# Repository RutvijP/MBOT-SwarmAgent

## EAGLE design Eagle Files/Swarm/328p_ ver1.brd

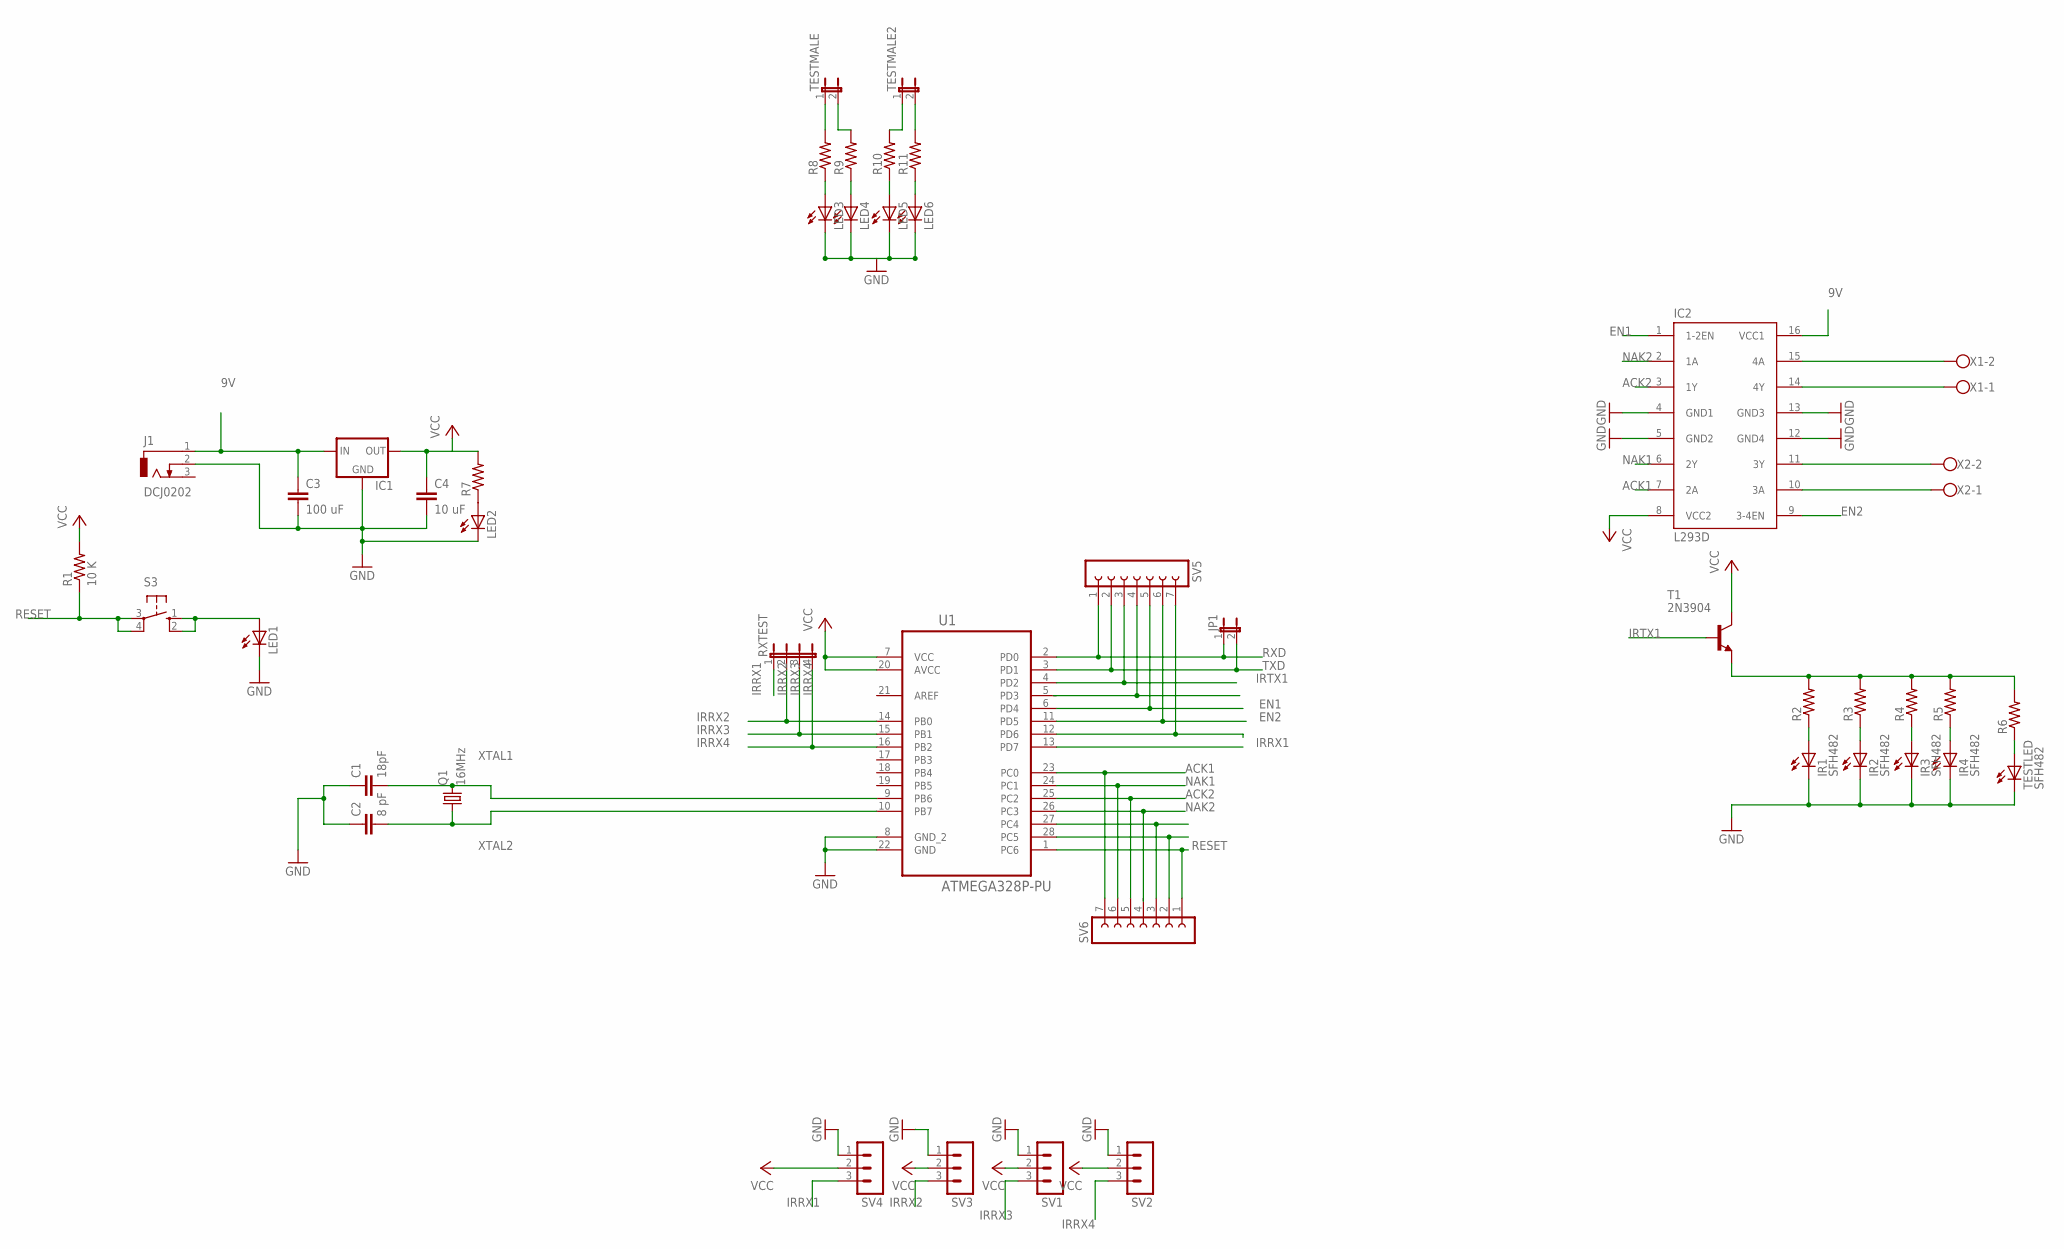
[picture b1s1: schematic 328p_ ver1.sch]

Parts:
C1: 18pF; C2.5-3
C2: 8 pF; C2.5-3
C3: 100 uF; C2.5-3
C4: 10 uF; C2.5-3
IC1: 78XXS
IC2: L293D; DIL16
IR1, IR2, IR3, IR4: SFH482
J1: DCJ0202
JP1: JP1E; JP1
LED1, LED2, LED3, LED4, LED5, LED6: LED3MM
Q1: 16MHz; HC49/S
R1: 10 K; 0207/12
R2, R3, R4, R5, R6, R7, R8, R9, R10, R11: R-US_0204/7; 0204/7
RXTEST: JP4E; JP4
S3: 10-XX; B3F-10XX
SV1, SV2, SV3, SV4: MA03-1
SV5, SV6: FE07-1; FE07
T1: 2N3904; TO92
TESTLED: SFH482
TESTMALE, TESTMALE2: JP1E; JP1
U1: ATMEGA328P-PU; DIP254P762X457-28
X1, X2: W237-102

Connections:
9V: C3.1, IC1.IN, IC2.16 (VCC1), J1.1
ACK1: IC2.7 (2A), SV6.7, U1.23 (PC0)
ACK2: IC2.3 (1Y), SV6.5, U1.25 (PC2)
EN1: IC2.1 (1-2EN), SV5.5, U1.6 (PD4)
EN2: IC2.9 (3-4EN), SV5.6, U1.11 (PD5)
GND: C1.1, C2.1, C3.2, C4.2, IC1.GND, IC2.4 (GND1), IC2.5 (GND2), IC2.12 (GND4), IC2.13 (GND3), IR1.K (C), IR2.K (C), IR3.K (C), IR4.K (C), J1.2, LED1.K (C), LED2.K (C), LED3.K (C), LED4.K (C), LED5.K (C), LED6.K (C), SV1.1, SV2.1, SV3.1, SV4.1, TESTLED.K (C), U1.8 (GND_2), U1.22 (GND)
IRRX1: RXTEST.1, SV4.3, U1.13 (PD7)
IRRX2: RXTEST.2, SV3.3, U1.14 (PB0)
IRRX3: RXTEST.3, SV1.3, U1.15 (PB1)
IRRX4: RXTEST.4, SV2.3, U1.16 (PB2)
IRTX1: SV5.3, T1.2 (B), U1.4 (PD2)
unnamed: IC2.15 (4A), X1.2
unnamed: IR1.A, R2.1
unnamed: IR2.A, R3.1
unnamed: IR3.A, R4.1
unnamed: IR4.A, R5.1
unnamed: R2.2, R3.2, R4.2, R5.2, R6.2, T1.3 (E)
unnamed: IC2.14 (4Y), X1.1
unnamed: IC2.11 (3Y), X2.2
unnamed: IC2.10 (3A), X2.1
unnamed: R6.1, TESTLED.A
unnamed: LED2.A, R7.1
unnamed: R8.2, TESTMALE.1
unnamed: LED3.A, R8.1
unnamed: LED1.A, S3.1 (S), S3.2 (S1)
unnamed: R9.2, TESTMALE.2
unnamed: LED4.A, R9.1
unnamed: R10.2, TESTMALE2.1
unnamed: R11.2, TESTMALE2.2
unnamed: LED6.A, R11.1
unnamed: LED5.A, R10.1
unnamed: SV5.7, U1.12 (PD6)
unnamed: SV6.3, U1.27 (PC4)
unnamed: SV6.2, U1.28 (PC5)
NAK1: IC2.6 (2Y), SV6.6, U1.24 (PC1)
NAK2: IC2.2 (1A), U1.26 (PC3)
RESET: R1.1, S3.3, S3.4 (P1), SV6.1, U1.1 (PC6)
RXD: JP1.1, SV5.1, U1.2 (PD0)
TXD: JP1.2, SV5.2, U1.3 (PD1)
VCC: C4.1, IC1.OUT, IC2.8 (VCC2), R1.2, R7.2, SV1.2, SV2.2, SV3.2, SV4.2, T1.1 (C), U1.7 (VCC), U1.20 (AVCC)
XTAL1: C1.2, Q1.2, U1.9 (PB6)
XTAL2: C2.2, Q1.1, U1.10 (PB7)

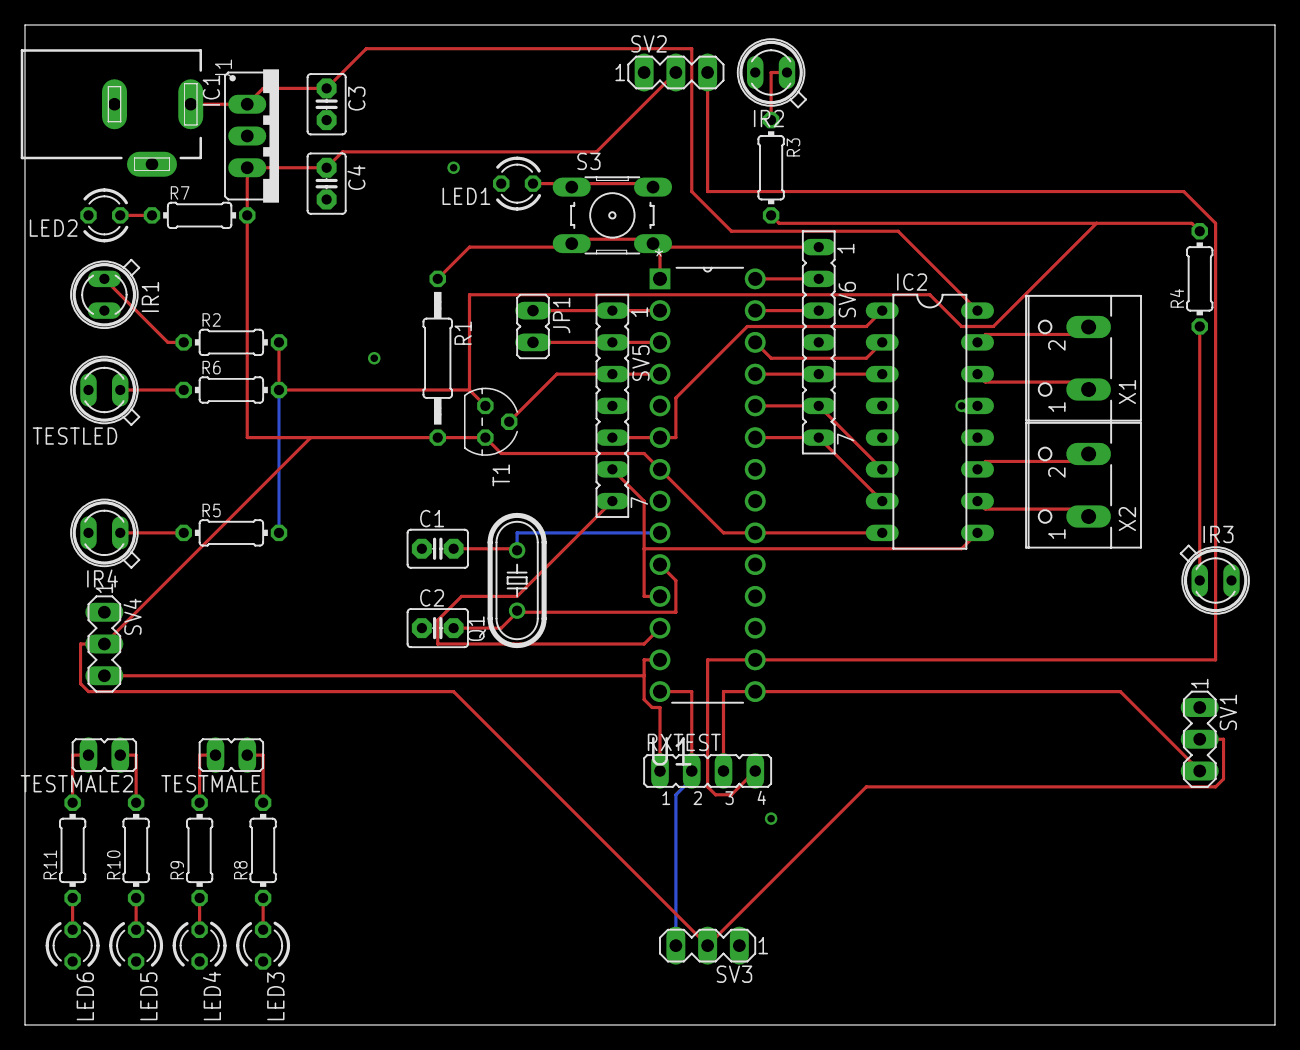
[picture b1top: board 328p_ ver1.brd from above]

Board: 2 copper layers, 100.0 x 80.0 mm, 45 parts (0 on the bottom side), 42 nets.

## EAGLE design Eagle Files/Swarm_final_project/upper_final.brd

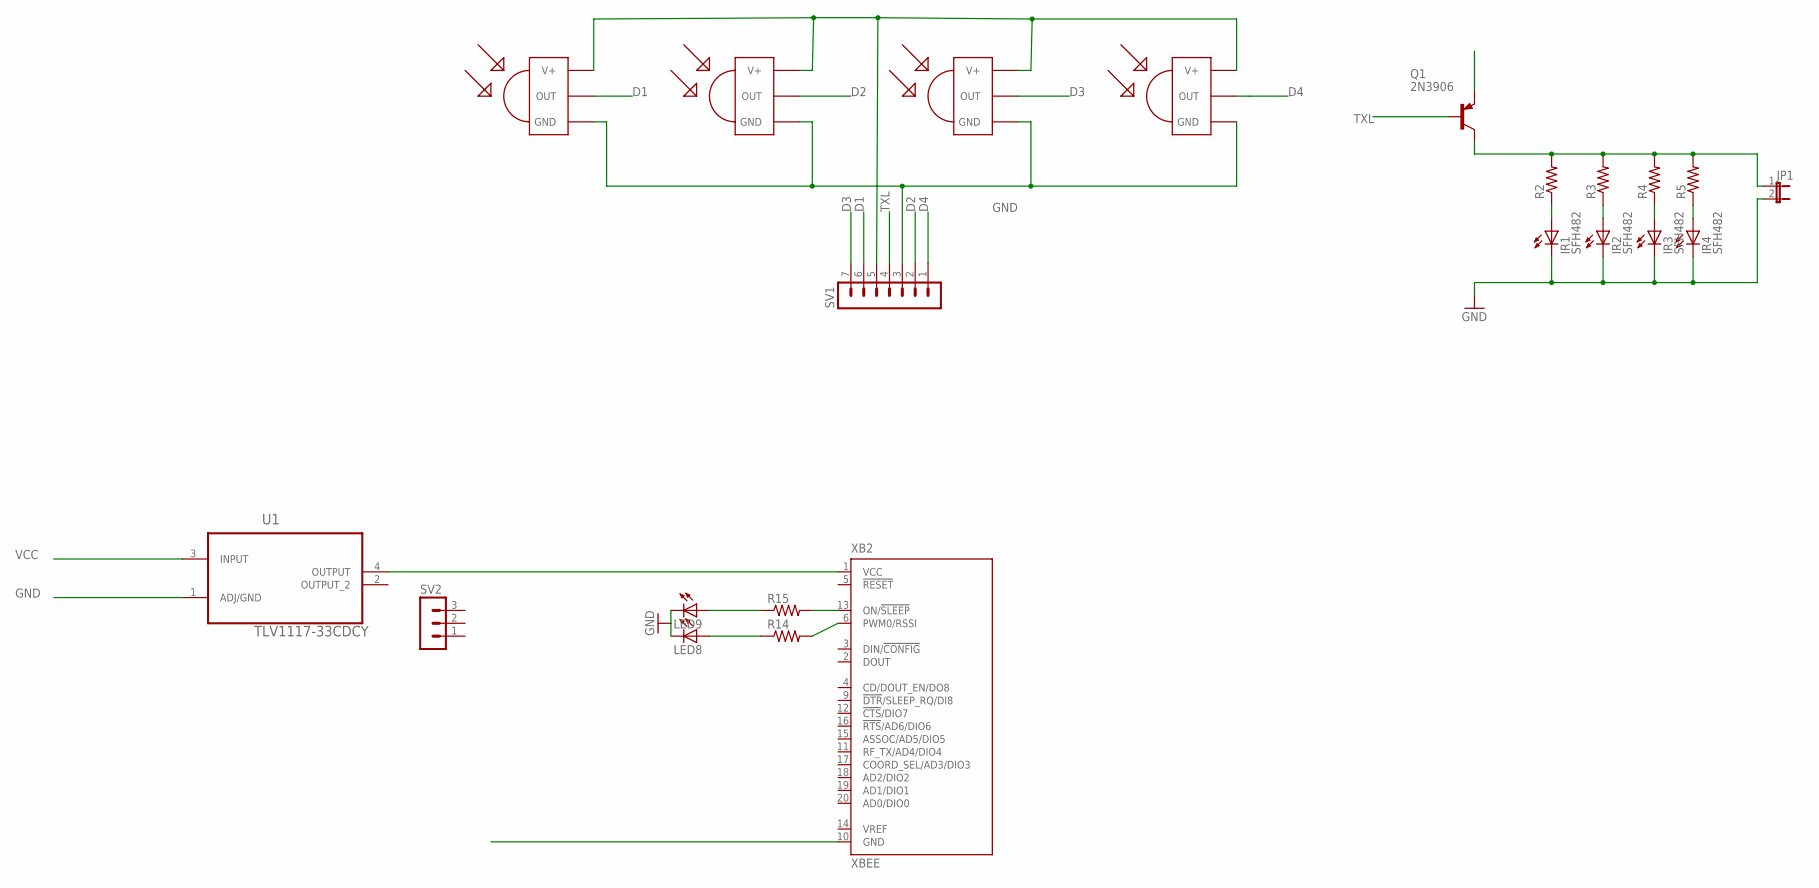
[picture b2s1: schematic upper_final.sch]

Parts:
IR1, IR2, IR3, IR4: SFH482
JP1: JP1E; JP1
LED8, LED9: LED3MM
Q1: 2N3906; TO92
R2, R3, R4, R5: R-US_0204/7; 0204/7
R14, R15: R-US_0207/10; 0207/10
SV1: MA07-1
SV2: MA03-1
U1: TLV1117-33CDCY; SOT230P700X180-4N
U$1, U$2, U$3, U$4: TSOP1738; TSOP17XX
XB2: XBEE

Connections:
D1: SV1.6, U$1.OUT
D2: SV1.2, U$2.OUT
D3: SV1.7, U$3.OUT
D4: SV1.1, U$4.OUT
GND: IR1.K (C), IR2.K (C), IR3.K (C), IR4.K (C), JP1.2, LED8.K (C), LED9.K (C), SV1.3, U1.1 (ADJ/GND), U$1.GND, U$2.GND, U$3.GND, U$4.GND, XB2.10 (GND)
unnamed: IR1.A, R2.1
unnamed: IR2.A, R3.1
unnamed: IR3.A, R4.1
unnamed: IR4.A, R5.1
unnamed: JP1.1, Q1.1 (C), R2.2, R3.2, R4.2, R5.2
unnamed: R15.2, XB2.13 (ON/!SLEEP)
unnamed: U1.4 (OUTPUT), XB2.1 (VCC)
unnamed: LED8.A, R14.1
unnamed: LED9.A, R15.1
unnamed: R14.2, XB2.6 (PWM0/RSSI)
TXL: Q1.2 (B), SV1.4
VCC: Q1.3 (E), SV1.5, U1.3 (INPUT), U$1.V+, U$2.V+, U$3.V+, U$4.V+

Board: 2 copper layers, 22 parts (0 on the bottom side), 17 nets, no tracks yet.

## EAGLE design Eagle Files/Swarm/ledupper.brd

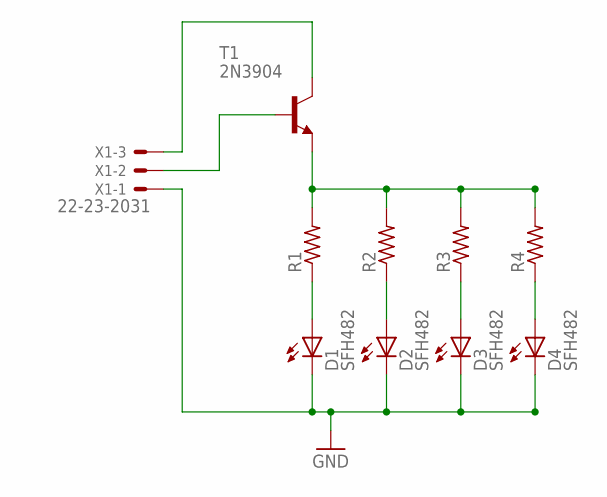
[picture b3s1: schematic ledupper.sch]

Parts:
D1, D2, D3, D4: SFH482
R1, R2, R3, R4: R-US_0204/7; 0204/7
T1: 2N3904; TO92
X1: 22-23-2031

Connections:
GND: D1.K (C), D2.K (C), D3.K (C), D4.K (C), X1.1
unnamed: T1.1 (C), X1.3
unnamed: T1.2 (B), X1.2
unnamed: D1.A, R1.1
unnamed: D2.A, R2.1
unnamed: D3.A, R3.1
unnamed: D4.A, R4.1
unnamed: R1.2, R2.2, R3.2, R4.2, T1.3 (E)

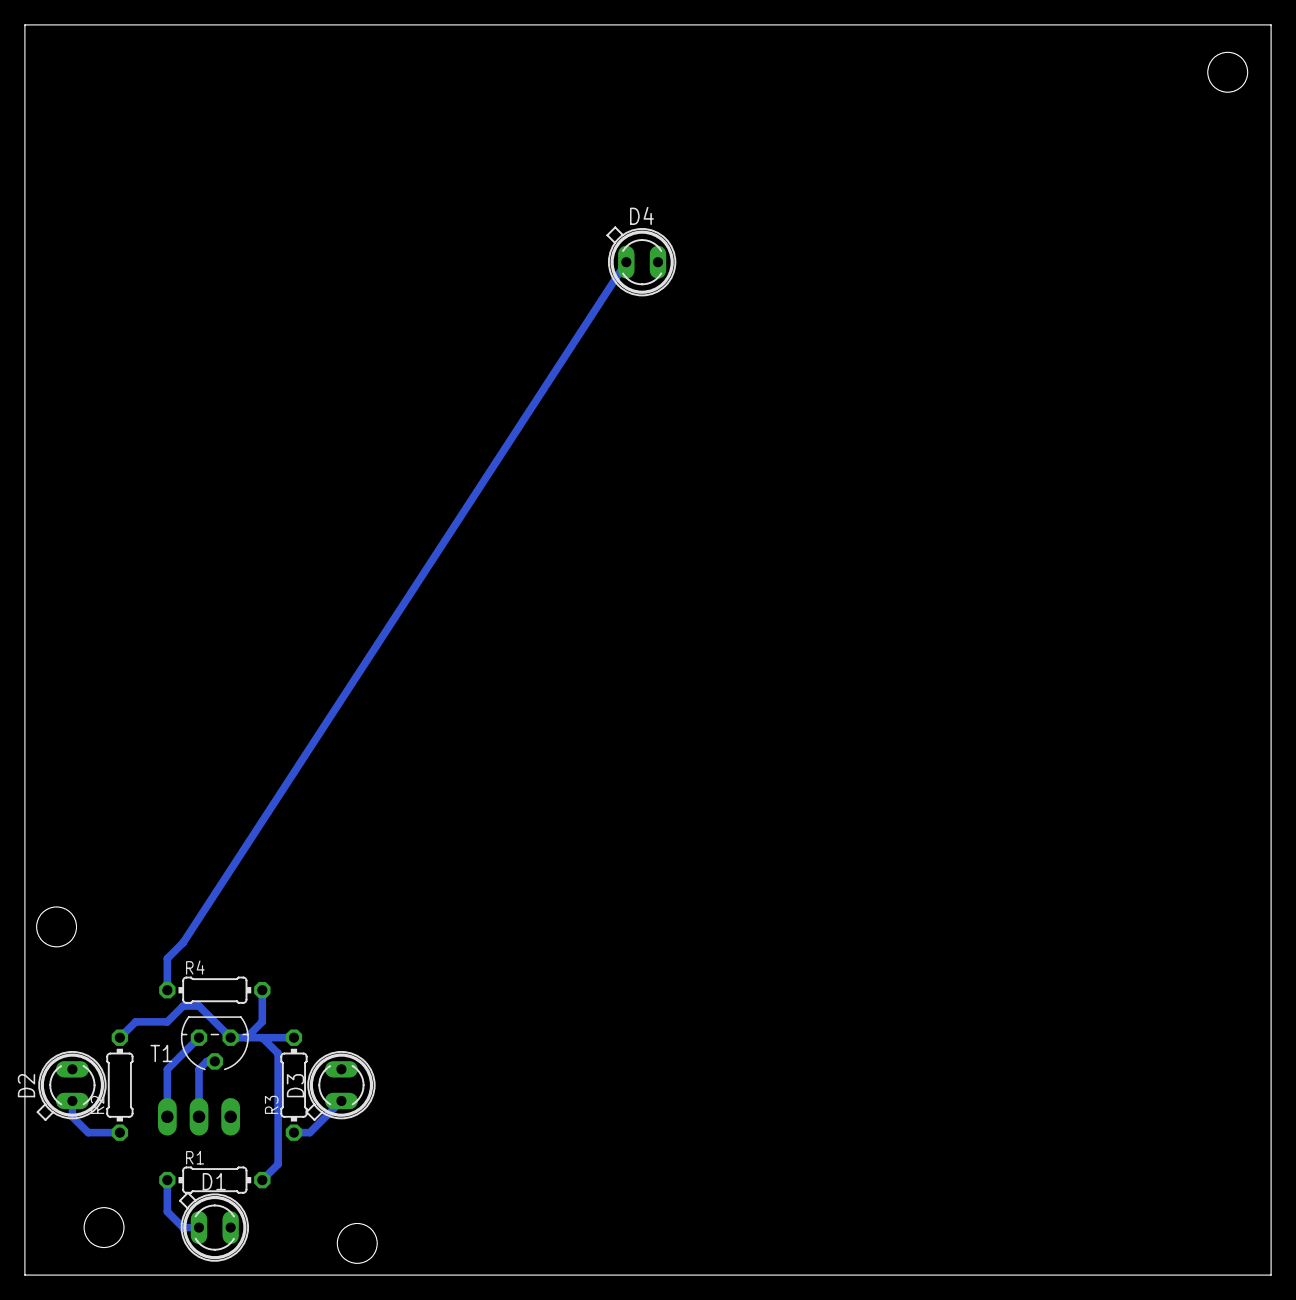
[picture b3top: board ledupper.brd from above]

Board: 2 copper layers, 100.0 x 100.3 mm, 10 parts (1 on the bottom side), 8 nets.

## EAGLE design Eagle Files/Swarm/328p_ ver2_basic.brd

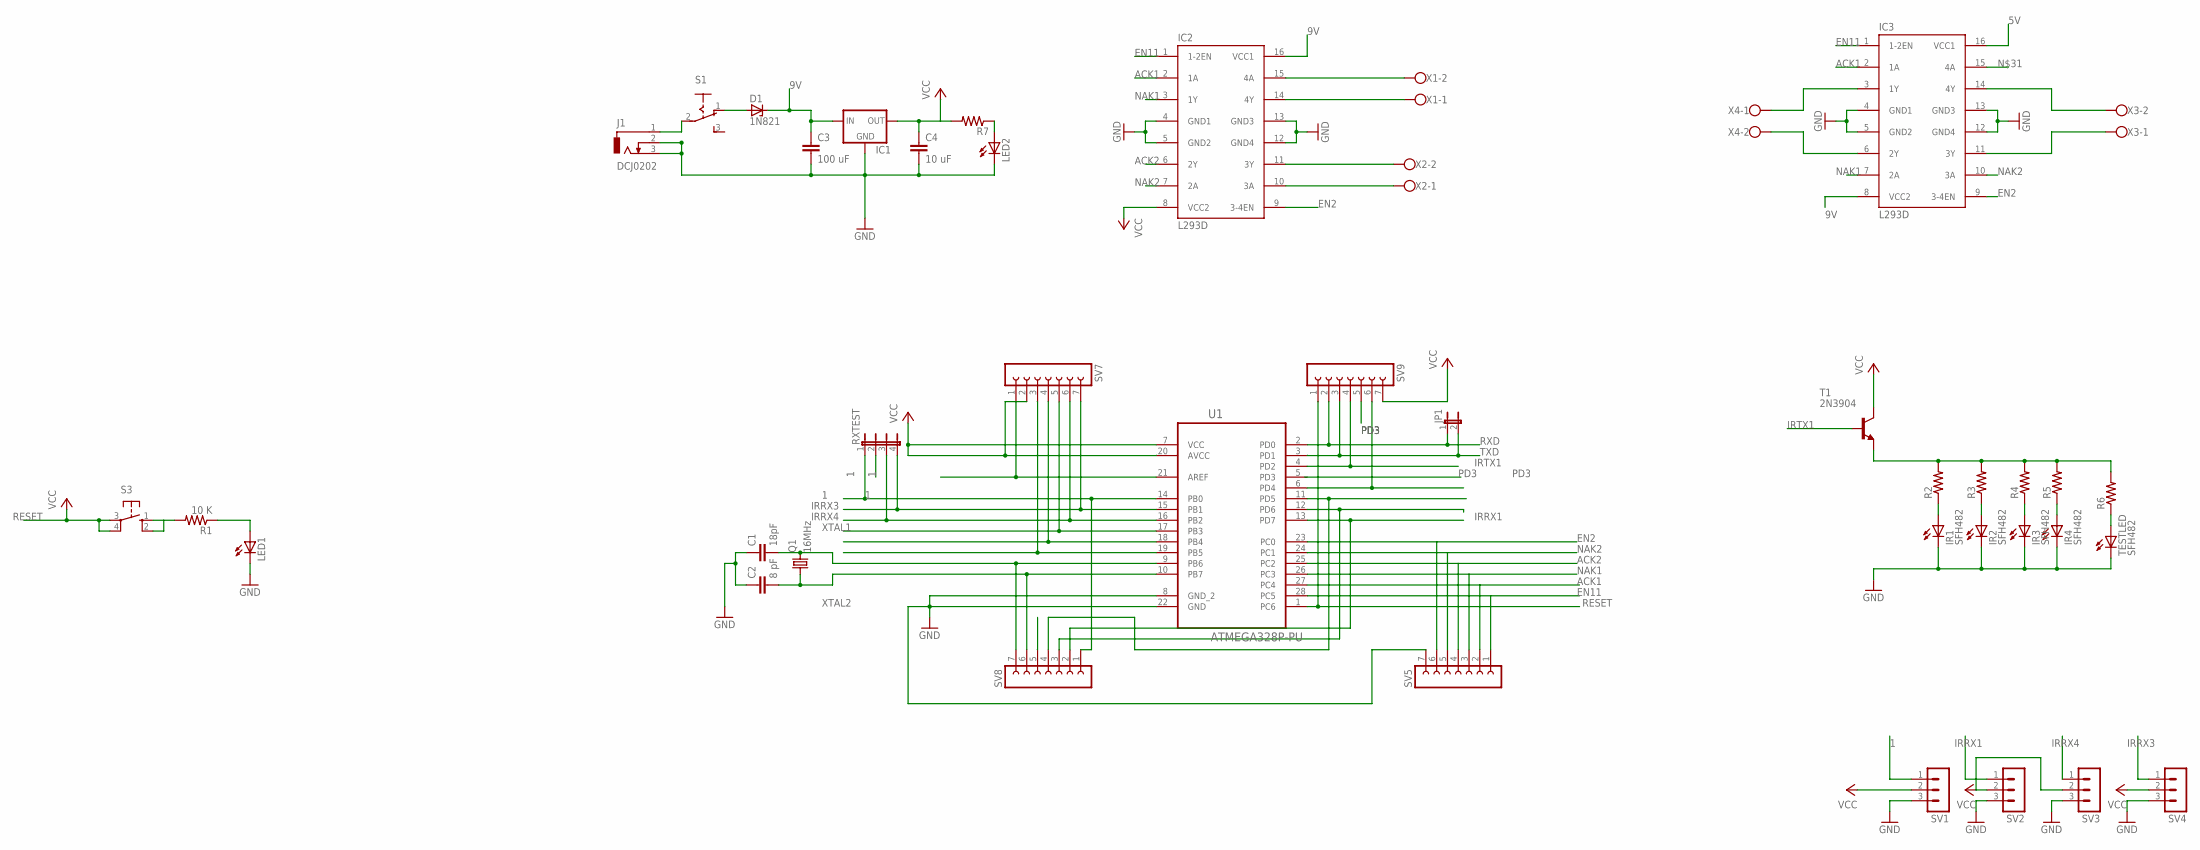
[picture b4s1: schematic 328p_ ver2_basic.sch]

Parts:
C1: 18pF; C2.5-3
C2: 8 pF; C2.5-3
C3: 100 uF; C2.5-3
C4: 10 uF; C2.5-3
D1: 1N821; DO35Z10
IC1: 78XXS
IC2, IC3: L293D; DIL16
IR1, IR2, IR3, IR4: SFH482
J1: DCJ0202
JP1: JP1E; JP1
LED1, LED2: LED3MM
Q1: 16MHz; HC49/S
R1: 10 K; 0207/12
R2, R3, R4, R5, R6, R7: R-US_0204/7; 0204/7
RXTEST: JP4E; JP4
S1: 255SB
S3: 10-XX; B3F-10XX
SV1, SV2, SV3, SV4: MA03-1
SV5, SV7, SV8, SV9: FE07-1; FE07
T1: 2N3904; TO92
TESTLED: SFH482
U1: ATMEGA328P-PU; DIP254P762X457-28
X1, X2, X3, X4: W237-102

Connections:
1: RXTEST.1, SV1.1, SV8.1, U1.14 (PB0)
5V: IC3.16 (VCC1)
9V: C3.1, D1.C, IC1.IN, IC2.16 (VCC1), IC3.8 (VCC2)
ACK1: IC2.2 (1A), IC3.2 (1A), SV5.2, U1.27 (PC4)
ACK2: IC2.6 (2Y), SV5.4, U1.25 (PC2)
EN1: SV8.5
EN2: IC2.9 (3-4EN), IC3.9 (3-4EN), SV5.6, U1.23 (PC0)
EN11: IC2.1 (1-2EN), IC3.1 (1-2EN), SV5.1, U1.28 (PC5)
GND: C1.1, C2.1, C3.2, C4.2, IC1.GND, IC2.4 (GND1), IC2.5 (GND2), IC2.12 (GND4), IC2.13 (GND3), IC3.4 (GND1), IC3.5 (GND2), IC3.12 (GND4), IC3.13 (GND3), IR1.K (C), IR2.K (C), IR3.K (C), IR4.K (C), J1.2, J1.3, LED1.K (C), LED2.K (C), SV1.3, SV2.3, SV3.3, SV4.3, SV5.7, TESTLED.K (C), U1.8 (GND_2), U1.22 (GND)
IRRX1: RXTEST.2, SV2.1, SV8.2, U1.13 (PD7)
IRRX3: RXTEST.4, SV4.1, SV7.7, U1.15 (PB1)
IRRX4: RXTEST.3, SV3.1, SV7.6, U1.16 (PB2)
IRTX1: SV9.4, T1.2 (B), U1.4 (PD2)
unnamed: IC2.15 (4A), X1.2
unnamed: IR1.A, R2.1
unnamed: IR2.A, R3.1
unnamed: IR3.A, R4.1
unnamed: IR4.A, R5.1
unnamed: R2.2, R3.2, R4.2, R5.2, R6.2, T1.3 (E)
unnamed: IC2.14 (4Y), X1.1
unnamed: IC2.11 (3Y), X2.2
unnamed: IC2.10 (3A), X2.1
unnamed: R6.1, TESTLED.A
unnamed: LED2.A, R7.1
unnamed: J1.1, S1.2
unnamed: R1.2, S3.1 (S), S3.2 (S1)
unnamed: SV7.5, U1.17 (PB3)
unnamed: SV7.4, U1.18 (PB4)
unnamed: SV7.3, U1.19 (PB5)
unnamed: SV7.1, U1.21 (AREF)
unnamed: LED1.A, R1.1
unnamed: SV9.6, U1.6 (PD4)
unnamed: C4.1, IC1.OUT, IC2.8 (VCC2), R7.2, SV1.2, SV2.2, SV3.2, SV4.2, SV7.2, SV9.7, T1.1 (C), U1.7 (VCC), U1.20 (AVCC)
unnamed: D1.A, S1.1 (O)
unnamed: SV8.3, U1.12 (PD6)
unnamed: IC3.14 (4Y), X3.2
unnamed: IC3.11 (3Y), X3.1
unnamed: IC3.6 (2Y), X4.2
NAK1: IC2.3 (1Y), IC3.3 (1Y), SV5.3, U1.26 (PC3), X4.1
NAK2: IC2.7 (2A), IC3.7 (2A), SV5.5, U1.24 (PC1)
PD3: SV9.5
PD5: SV8.4, U1.11 (PD5)
RESET: S3.3, S3.4 (P1), SV9.1, U1.1 (PC6)
RXD: JP1.1, SV9.2, U1.2 (PD0)
TXD: JP1.2, SV9.3, U1.3 (PD1)
XTAL1: C1.2, Q1.2, SV8.7, U1.9 (PB6)
XTAL2: C2.2, Q1.1, SV8.6, U1.10 (PB7)

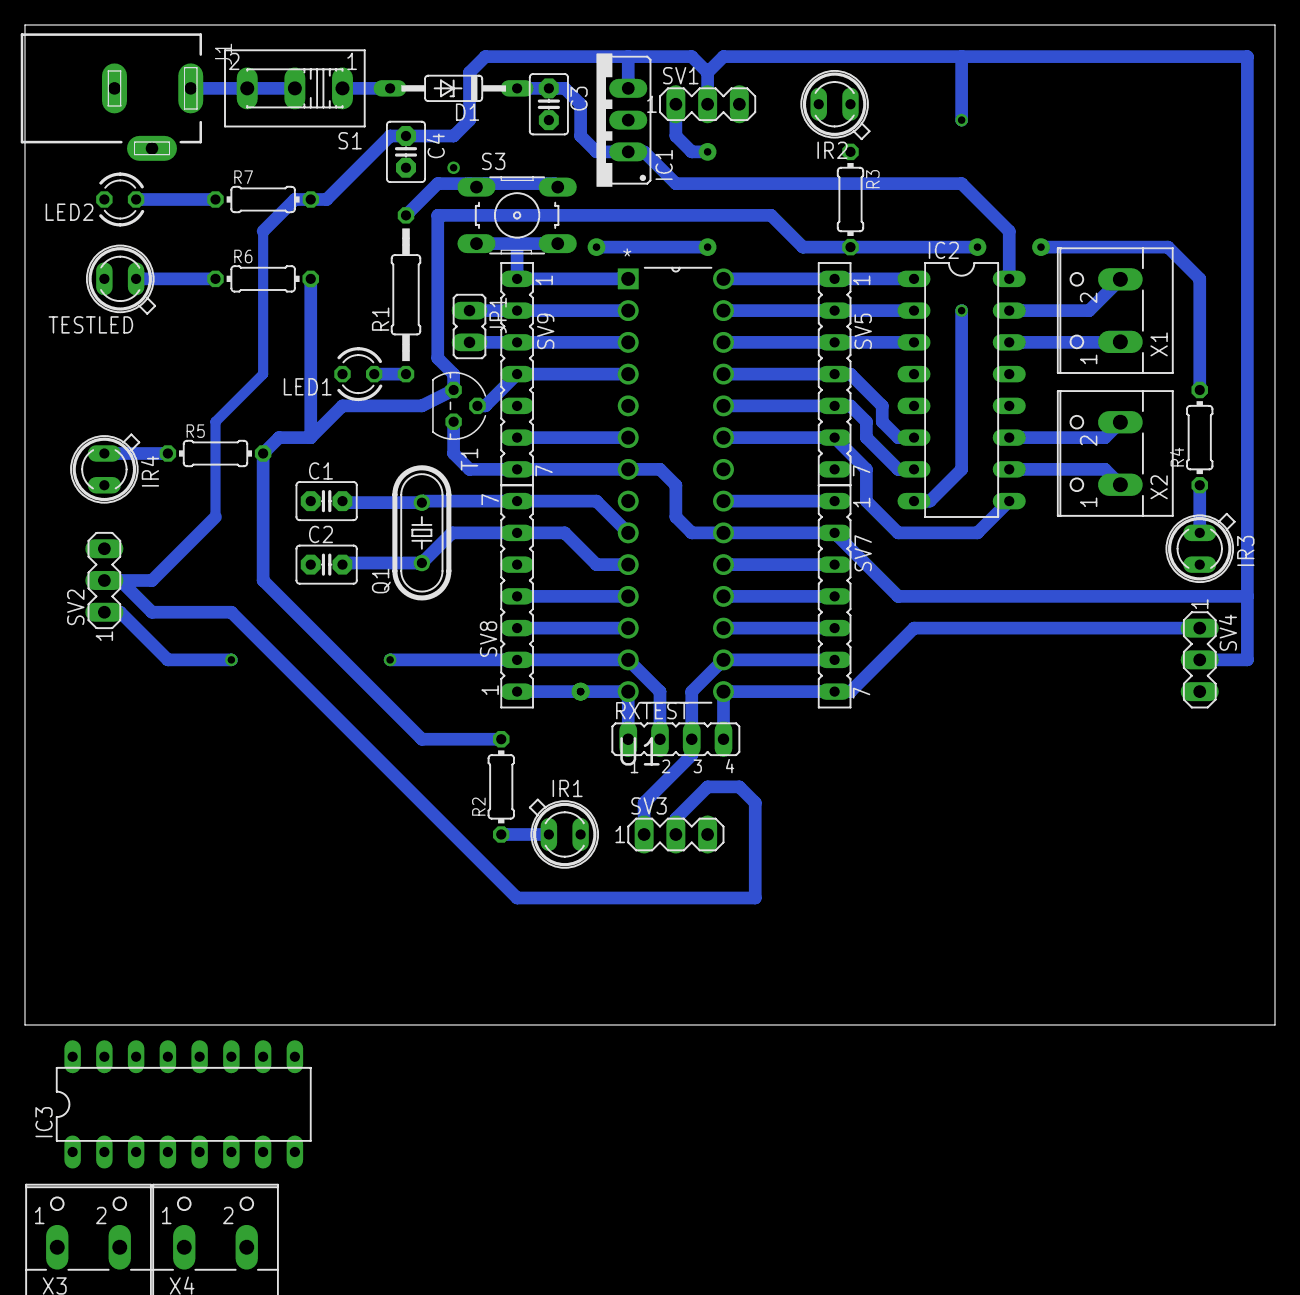
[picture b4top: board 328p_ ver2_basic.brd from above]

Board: 2 copper layers, 100.0 x 80.0 mm, 42 parts (0 on the bottom side), 44 nets.

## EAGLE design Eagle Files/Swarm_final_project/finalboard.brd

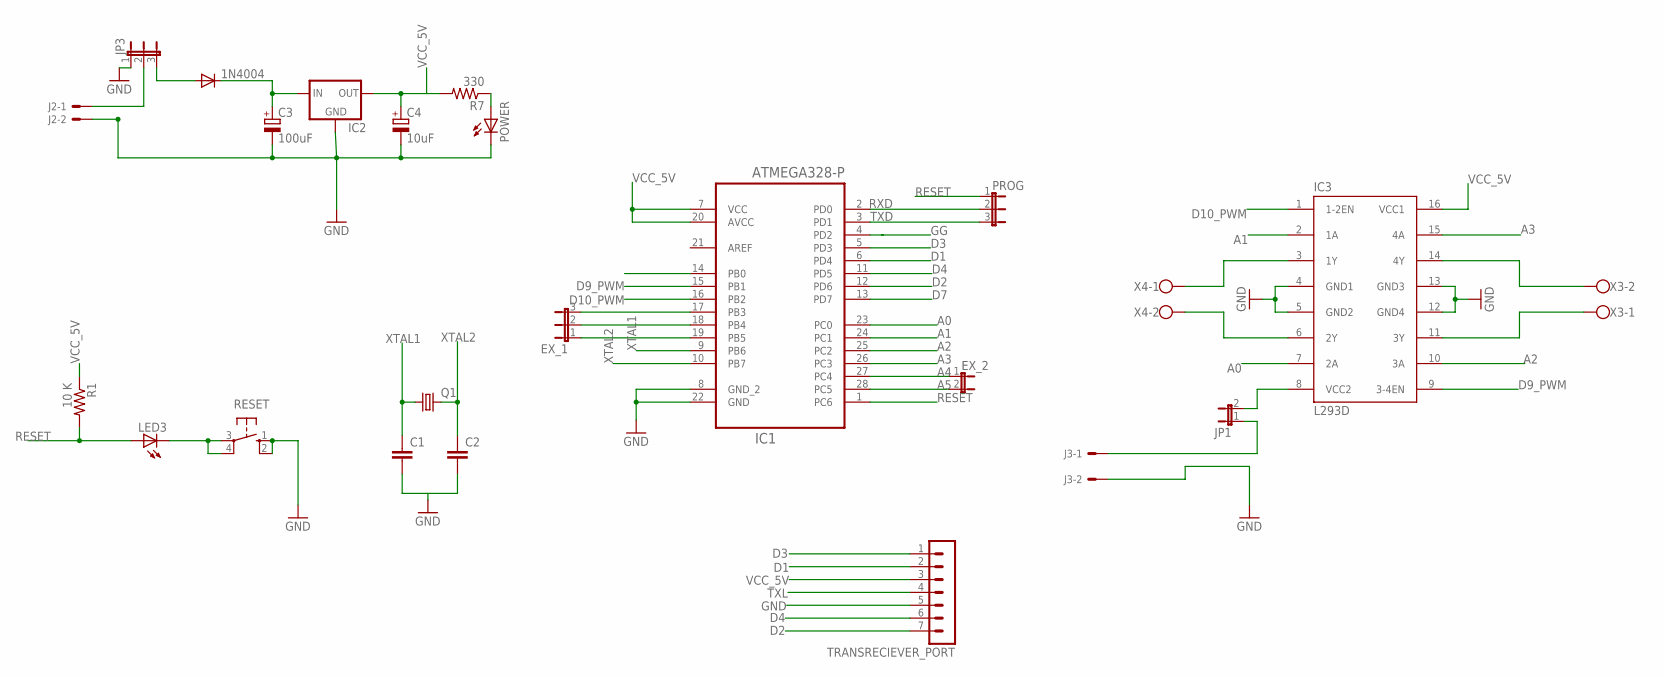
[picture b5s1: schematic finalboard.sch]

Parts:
1N4004: 1N4004; DO41-10
ATMEGA328-P: IC1; DIP254P762X457-28
C1, C2: C-EU025-025X050; C025-025X050
C3: 100uF; E2,5-6E
C4: 10uF; E2-5
EX_1: JP2E; JP2
EX_2: JP1E; JP1
IC2: 78XXL
IC3: L293D; DIL16
J2, J3: 22-05-7028-02; 7395-02
JP1: JP1E; JP1
JP3: JP2E; JP2
LED3: LED3MM
POWER: LED3MM
PROG: JP2E; JP2
Q1: CRYSTALHC49U70; HC49U70
R1: 10 K; 0207/12
R7: 330; 0204/7
RESET: 10-XX; B3F-10XX
TRANSRECIEVER_PORT: MA07-1
X3, X4: W237-102

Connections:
A0: ATMEGA328-P.23 (PC0), IC3.7 (2A)
A1: ATMEGA328-P.24 (PC1), IC3.2 (1A)
A2: ATMEGA328-P.25 (PC2), IC3.10 (3A)
A3: ATMEGA328-P.26 (PC3), IC3.15 (4A)
A4: ATMEGA328-P.27 (PC4), EX_2.1
A5: ATMEGA328-P.28 (PC5), EX_2.2
D1: ATMEGA328-P.6 (PD4), TRANSRECIEVER_PORT.2
D2: ATMEGA328-P.12 (PD6), TRANSRECIEVER_PORT.7
D3: ATMEGA328-P.5 (PD3), TRANSRECIEVER_PORT.1
D4: ATMEGA328-P.11 (PD5), TRANSRECIEVER_PORT.6
D7: ATMEGA328-P.13 (PD7)
D9_PWM: ATMEGA328-P.15 (PB1), IC3.9 (3-4EN)
D10_PWM: ATMEGA328-P.16 (PB2), IC3.1 (1-2EN)
GG: ATMEGA328-P.4 (PD2)
GND: ATMEGA328-P.8 (GND_2), ATMEGA328-P.22 (GND), C1.2, C2.2, C3.-, C4.-, IC2.GND, IC3.4 (GND1), IC3.5 (GND2), IC3.12 (GND4), IC3.13 (GND3), J2.2, J3.2, JP3.1, POWER.K (C), RESET.1 (S), RESET.2 (S1), TRANSRECIEVER_PORT.5
unnamed: LED3.K (C), RESET.3, RESET.4 (P1)
unnamed: ATMEGA328-P.17 (PB3), EX_1.3
unnamed: ATMEGA328-P.18 (PB4), EX_1.2
unnamed: ATMEGA328-P.19 (PB5), EX_1.1
unnamed: J3.1, JP1.1
unnamed: IC3.8 (VCC2), JP1.2
unnamed: POWER.A, R7.1
unnamed: J2.1, JP3.2
unnamed: 1N4004.A, JP3.3
unnamed: IC3.14 (4Y), X3.2
unnamed: IC3.11 (3Y), X3.1
unnamed: IC3.6 (2Y), X4.2
NAK1: IC3.3 (1Y), X4.1
RESET: ATMEGA328-P.1 (PC6), LED3.A, PROG.1, R1.2
RXD: ATMEGA328-P.2 (PD0), PROG.2
TXD: ATMEGA328-P.3 (PD1), PROG.3
TXL: ATMEGA328-P.14 (PB0), TRANSRECIEVER_PORT.4
VCC_5V: ATMEGA328-P.7 (VCC), ATMEGA328-P.20 (AVCC), C4.+, IC2.OUT, IC3.16 (VCC1), R1.1, R7.2, TRANSRECIEVER_PORT.3
VCC_9V: 1N4004.C, C3.+, IC2.IN
XTAL1: ATMEGA328-P.9 (PB6), C1.1, Q1.1
XTAL2: ATMEGA328-P.10 (PB7), C2.1, Q1.2

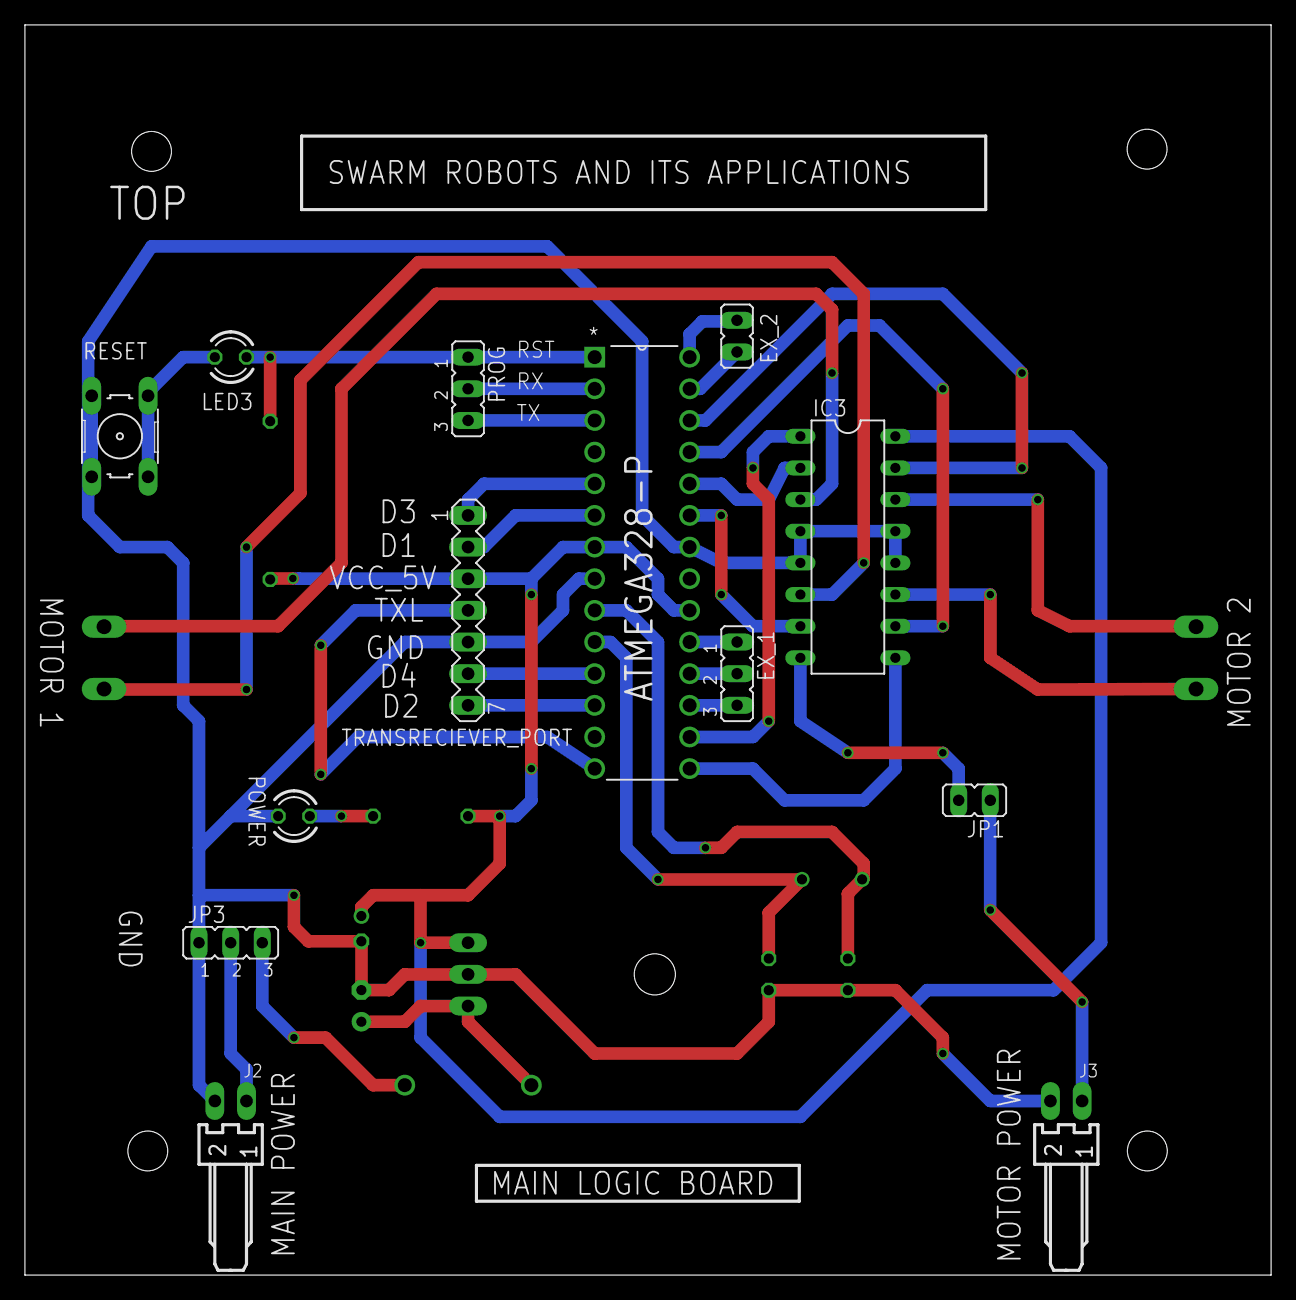
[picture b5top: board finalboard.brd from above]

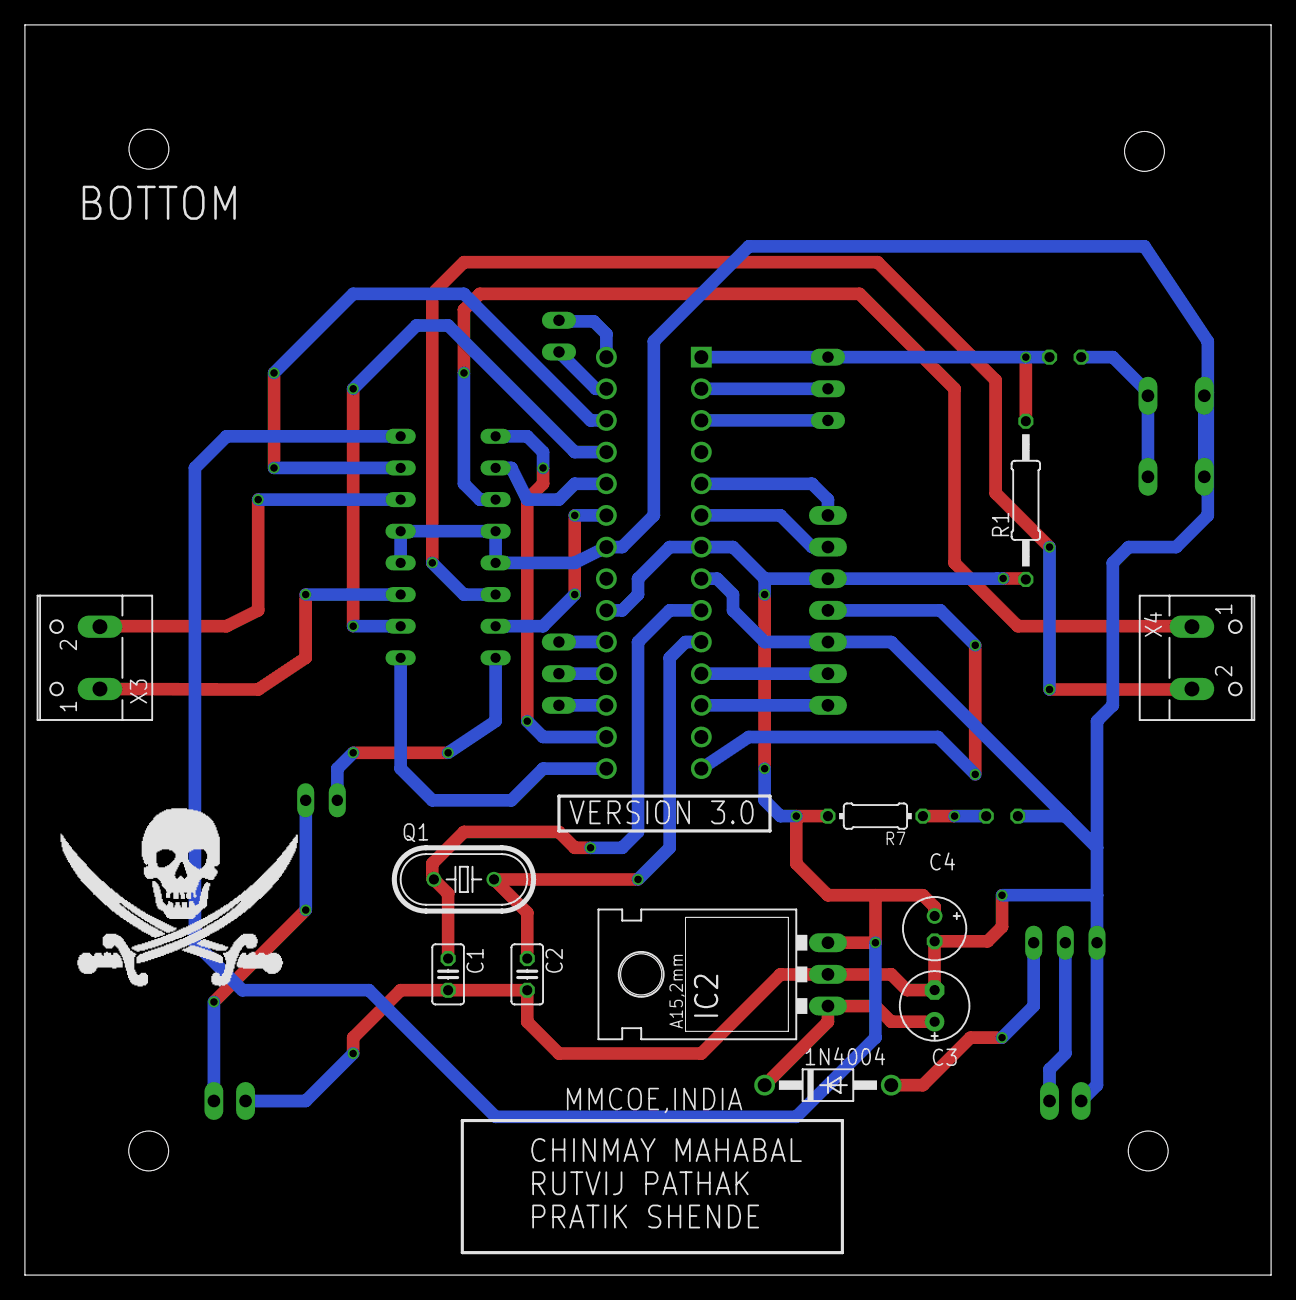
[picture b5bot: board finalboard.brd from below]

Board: 2 copper layers, 100.0 x 100.3 mm, 24 parts (11 on the bottom side), 34 nets.

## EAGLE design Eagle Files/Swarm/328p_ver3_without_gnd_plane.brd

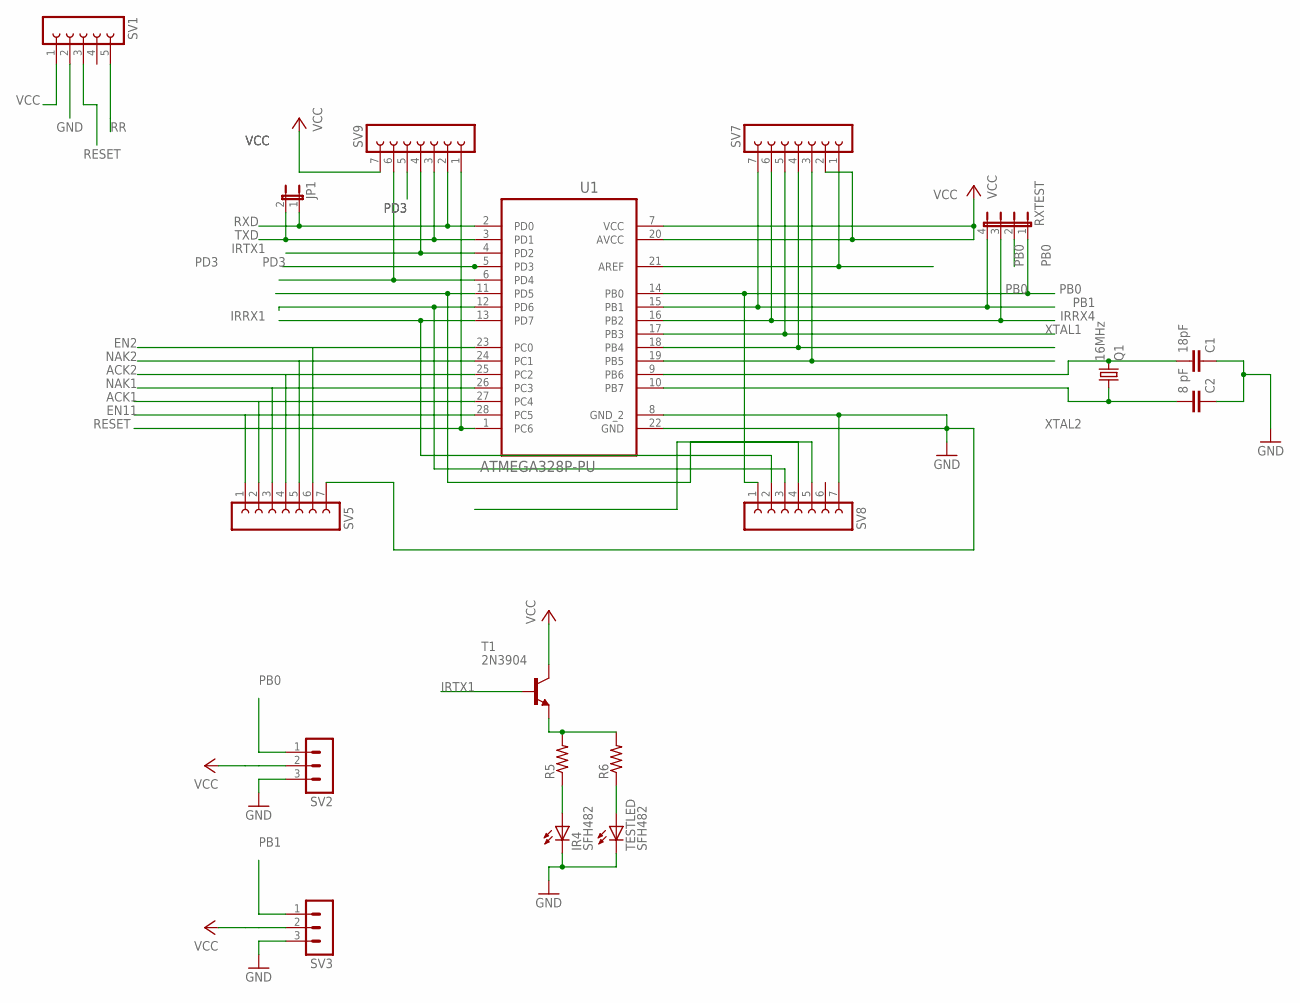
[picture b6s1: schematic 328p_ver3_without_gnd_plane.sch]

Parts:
C1: 18pF; C2.5-3
C2: 8 pF; C2.5-3
IR4: SFH482
JP1: JP1E; JP1
Q1: 16MHz; HC49/S
R5, R6: R-US_0204/7; 0204/7
RXTEST: JP4E; JP4
SV1: FE05-1
SV2, SV3: MA03-1
SV5, SV7, SV8, SV9: FE07-1; FE07
T1: 2N3904; TO92
TESTLED: SFH482
U1: ATMEGA328P-PU; DIP254P762X457-28

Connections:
ACK1: SV5.2, U1.27 (PC4)
ACK2: SV5.4, U1.25 (PC2)
EN1: SV8.5
EN2: SV5.6, U1.23 (PC0)
EN11: SV5.1, U1.28 (PC5)
GND: C1.1, C2.1, IR4.K (C), SV1.2, SV2.3, SV3.3, SV5.7, SV8.7, TESTLED.K (C), U1.8 (GND_2), U1.22 (GND)
IRRX1: RXTEST.2, SV8.2, U1.13 (PD7)
IRRX4: RXTEST.3, SV7.6, U1.16 (PB2)
IRTX1: SV9.4, T1.2 (B), U1.4 (PD2)
unnamed: IR4.A, R5.1
unnamed: R5.2, R6.2, T1.3 (E)
unnamed: R6.1, TESTLED.A
unnamed: SV7.5, U1.17 (PB3)
unnamed: SV7.4, U1.18 (PB4)
unnamed: SV7.3, U1.19 (PB5)
unnamed: SV7.1, U1.21 (AREF)
unnamed: SV9.6, U1.6 (PD4)
unnamed: SV2.2, SV3.2, T1.1 (C)
unnamed: SV8.3, U1.12 (PD6)
NAK1: SV5.3, U1.26 (PC3)
NAK2: SV5.5, U1.24 (PC1)
PB0: RXTEST.1, SV2.1, SV8.1, U1.14 (PB0)
PB1: RXTEST.4, SV3.1, SV7.7, U1.15 (PB1)
PD3: SV9.5, U1.5 (PD3)
PD5: SV8.4, U1.11 (PD5)
RESET: SV1.3, SV9.1, U1.1 (PC6)
RR: SV1.5
RXD: JP1.1, SV9.2, U1.2 (PD0)
TXD: JP1.2, SV9.3, U1.3 (PD1)
VCC: SV1.1, SV7.2, SV9.7, U1.7 (VCC), U1.20 (AVCC)
XTAL1: C1.2, Q1.2, U1.9 (PB6)
XTAL2: C2.2, Q1.1, U1.10 (PB7)
